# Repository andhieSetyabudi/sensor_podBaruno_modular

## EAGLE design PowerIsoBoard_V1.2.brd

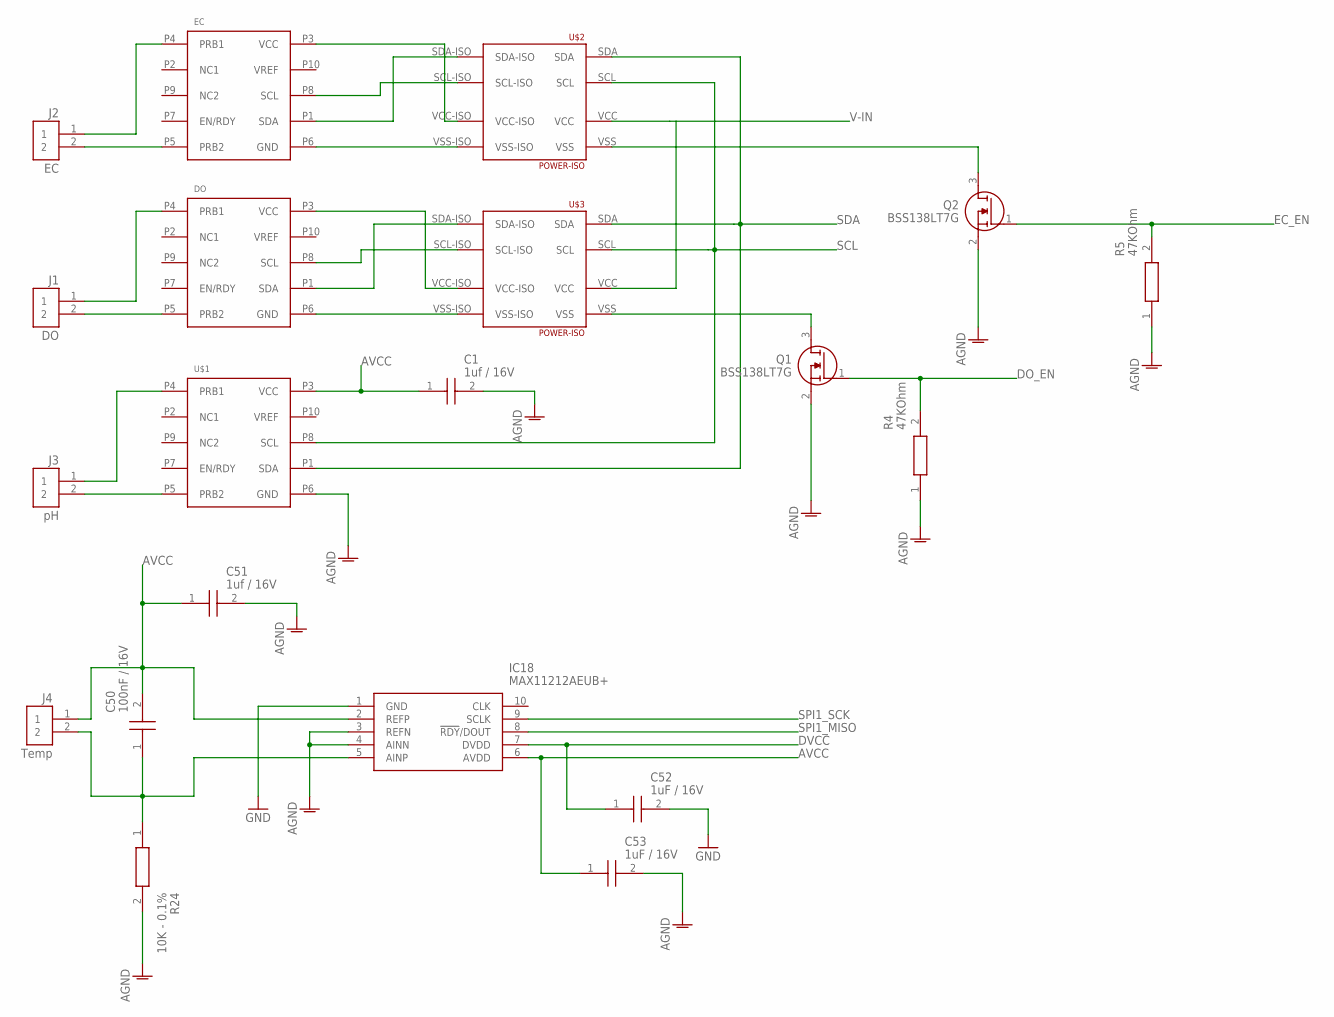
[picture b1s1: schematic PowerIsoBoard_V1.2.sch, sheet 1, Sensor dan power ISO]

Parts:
C1, C51: 1uf / 16V; CAPC1608X90N
C50: 100nF / 16V; CAPC1608X90N
C52, C53: 1uF / 16V; CAPC1608X90N
DO: ATLAS-OEM-SMT; EZO_SMT
EC: ATLAS-OEM-SMT; EZO_SMT
IC18: MAX11212AEUB+; SOP50P490X110-10N
J1: DO; JST_B2B-PH-K-S(LF)(SN)
J2: EC; JST_B2B-PH-K-S(LF)(SN)
J3: pH; JST_B2B-PH-K-S(LF)(SN)
J4: Temp; JST_B2B-PH-K-S(LF)(SN)
Q1, Q2: BSS138LT7G; SOT96P237X111-3N
R4, R5: 47KOhm; RESC1608X55N
R24: 10K - 0.1%; RESC1608X55N
U$1: ATLAS-OEM-SMT; EZO_SMT
U$2, U$3: POWER-ISO; PWR_ISO_TH

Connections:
AGND: C1.2, Q1.2 (S), Q2.2 (S), R4.1, R5.1, U$1.P6 (GND); also elsewhere on the board
AVCC: C1.1, C50.2, C51.1, C53.1, IC18.2 (REFP), IC18.6 (AVDD), J4.1, U$1.P3 (VCC); also elsewhere on the board
DO_EN: Q1.1 (G), R4.2; also elsewhere on the board
DVCC: C52.1, IC18.7 (DVDD); also elsewhere on the board
EC_EN: Q2.1 (G), R5.2; also elsewhere on the board
GND: C51.2, C52.2, C53.2, IC18.1 (GND), IC18.3 (REFN), IC18.4 (AINN), R24.2; also elsewhere on the board
unnamed: C50.1, IC18.5 (AINP), J4.2, R24.1
unnamed: Q1.3 (D), U$3.VSS
unnamed: J3.2, U$1.P5 (PRB2)
unnamed: J3.1, U$1.P4 (PRB1)
unnamed: DO.P5 (PRB2), J1.2
unnamed: DO.P4 (PRB1), J1.1
unnamed: EC.P5 (PRB2), J2.2
unnamed: EC.P4 (PRB1), J2.1
unnamed: EC.P6 (GND), U$2.VSS-ISO
unnamed: EC.P3 (VCC), U$2.VCC-ISO
unnamed: EC.P8 (SCL), U$2.SCL-ISO
unnamed: EC.P1 (SDA), U$2.SDA-ISO
unnamed: DO.P6 (GND), U$3.VSS-ISO
unnamed: DO.P3 (VCC), U$3.VCC-ISO
unnamed: DO.P1 (SDA), U$3.SDA-ISO
unnamed: DO.P8 (SCL), U$3.SCL-ISO
unnamed: Q2.3 (D), U$2.VSS
SCL: U$1.P8 (SCL), U$2.SCL, U$3.SCL; also elsewhere on the board
SDA: U$1.P1 (SDA), U$2.SDA, U$3.SDA; also elsewhere on the board
SPI1_MISO: IC18.8 (!RDY!/DOUT); also elsewhere on the board
SPI1_SCK: IC18.9 (SCLK); also elsewhere on the board
V-IN: U$2.VCC, U$3.VCC; also elsewhere on the board

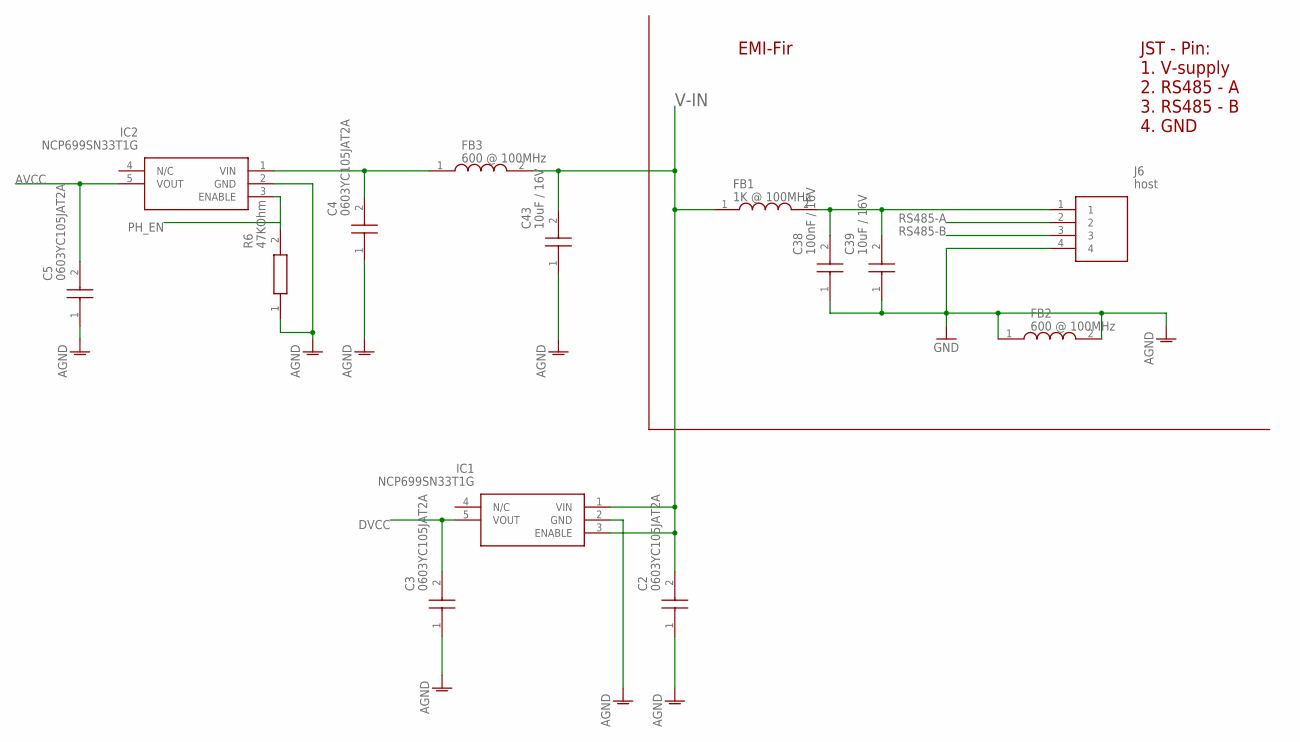
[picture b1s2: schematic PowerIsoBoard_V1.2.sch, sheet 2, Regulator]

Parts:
C2, C3, C4, C5: 0603YC105JAT2A; CAPC1608X90N
C38: 100nF / 16V; CAPC1608X90N
C39, C43: 10uF / 16V; CAPC1608X100N
FB1: 1K @ 100MHz; BLM18KG102SH1J
FB2, FB3: 600 @ 100MHz; BEADC1608X75N
IC1, IC2: NCP699SN33T1G; SOT95P275X110-5N
J6: host; SHDR4W50P0X200_1X4_990X450X600
R6: 47KOhm; RESC1608X55N

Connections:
AGND: C2.1, C3.1, C4.1, C5.1, C43.1, IC1.2 (GND), IC2.2 (GND), R6.1; also elsewhere on the board
AVCC: C5.2, IC2.5 (VOUT); also elsewhere on the board
DVCC: C3.2, IC1.5 (VOUT); also elsewhere on the board
GND: C38.1, C39.1, FB2.1, FB2.2, J6.4; also elsewhere on the board
unnamed: C38.2, C39.2, FB1.2, J6.1
unnamed: C4.2, FB3.1, IC2.1 (VIN)
PH_EN: IC2.3 (ENABLE), R6.2; also elsewhere on the board
RS485-A: J6.2; also elsewhere on the board
RS485-B: J6.3; also elsewhere on the board
V-IN: C2.2, C43.2, FB1.1, FB3.2, IC1.1 (VIN), IC1.3 (ENABLE); also elsewhere on the board

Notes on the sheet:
EMI-Fir
JST - Pin: 1. V-supply 2. RS485 - A 3. RS485 - B 4. GND

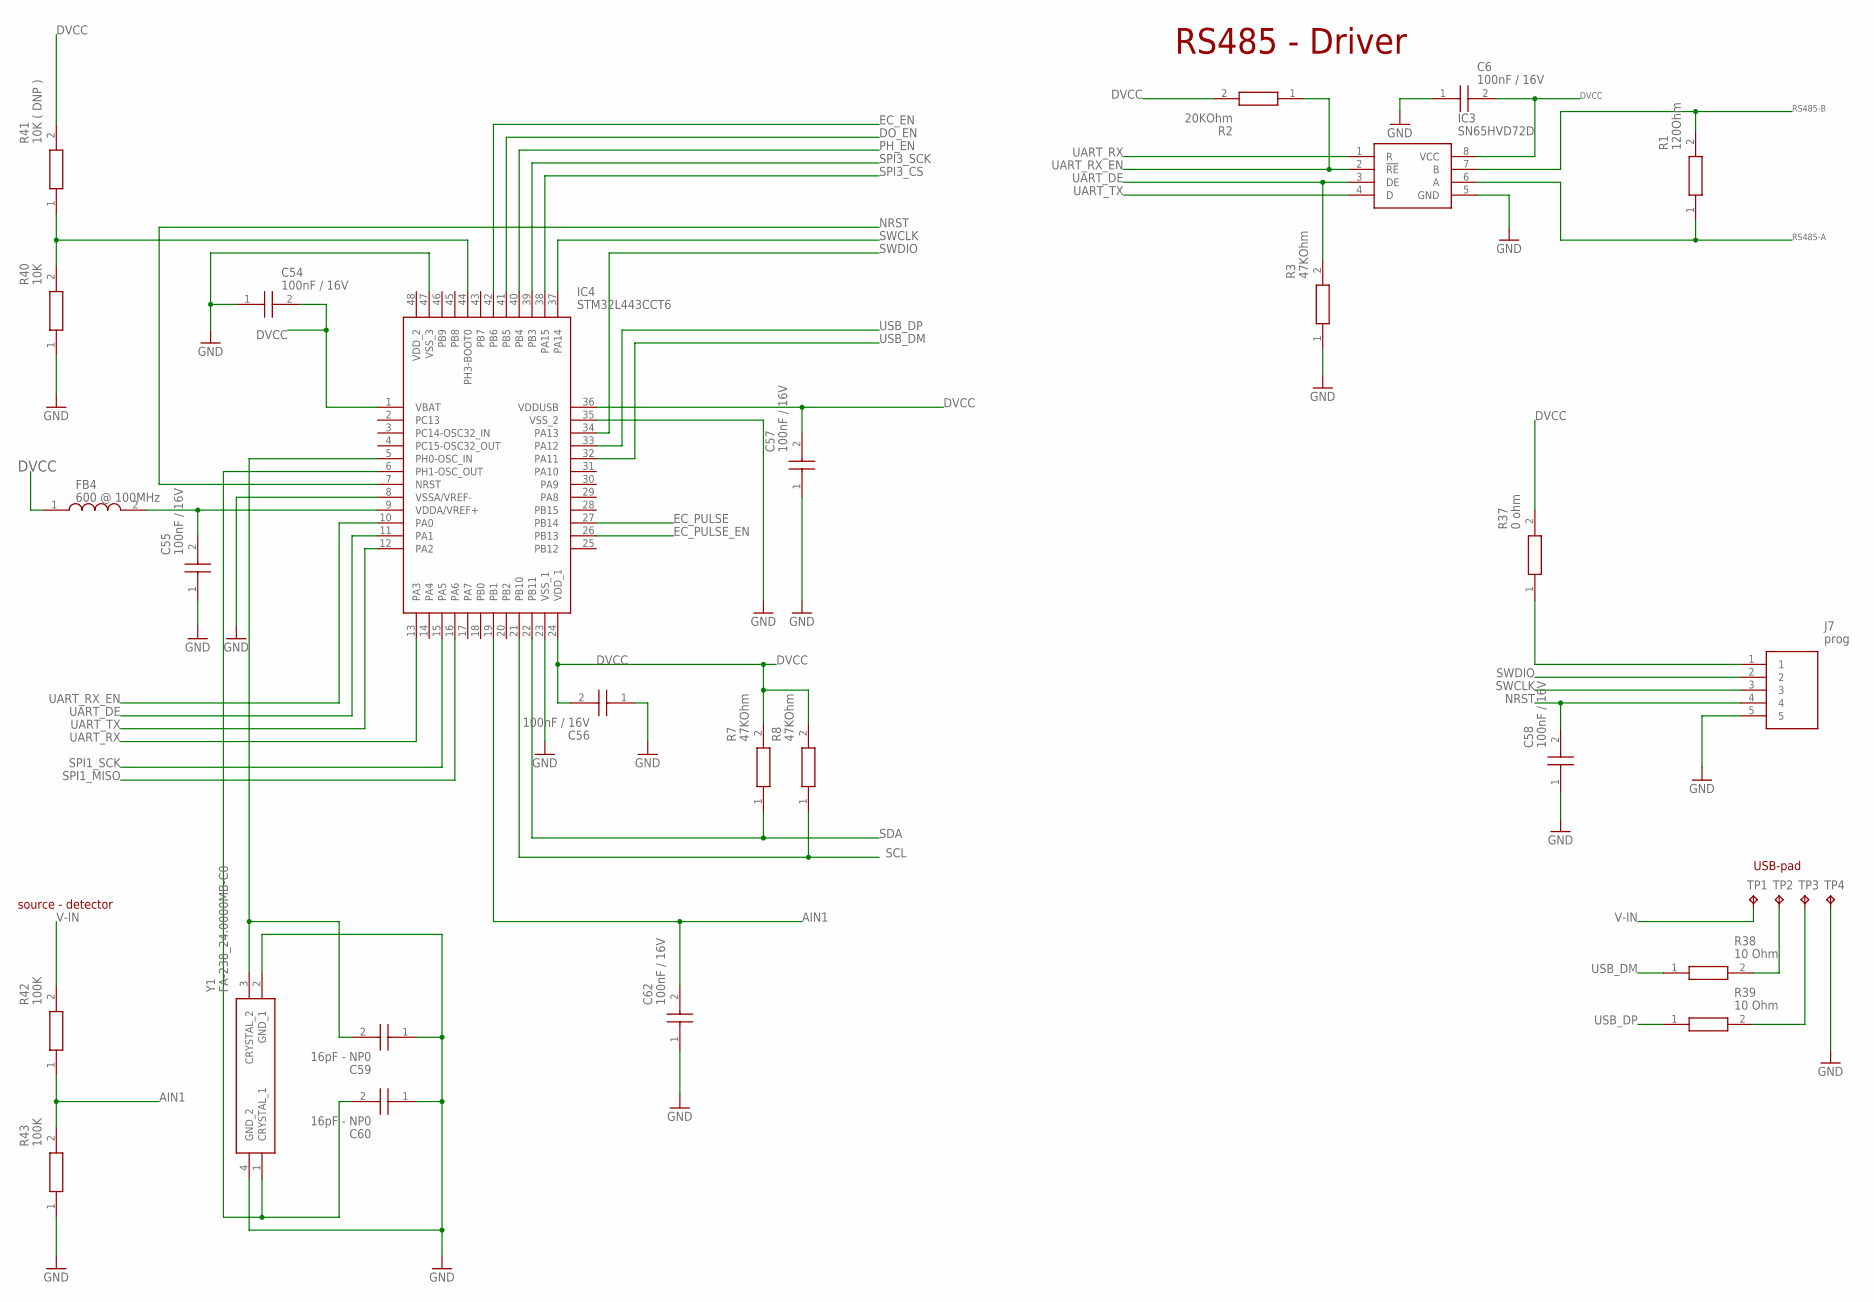
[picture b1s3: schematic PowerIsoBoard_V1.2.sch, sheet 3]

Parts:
C6, C54, C55, C56, C57, C58, C62: 100nF / 16V; CAPC1608X90N
C59, C60: 16pF - NP0; CAPC1608X97N
FB4: 600 @ 100MHz; BEADC1608X75N
IC3: SN65HVD72D; SOIC127P600X175-8N
IC4: STM32L443CCT6; QFP50P900X900X160-48N
J7: prog; SHDR5W50P0X200_1X5_1190X450X60
R1: 120Ohm; RESC1608X55N
R2: 20KOhm; RESC1608X55N
R3, R7, R8: 47KOhm; RESC1608X55N
R37: 0 ohm; RESC1608X55N
R38, R39: 10 Ohm; RESC1608X55N
R40: 10K; RESC1608X55N
R41: 10K ( DNP ); RESC1608X55N
R42, R43: 100K; RESC1608X55N
TP1, TP2, TP3, TP4: TPB1,27; B1,27
Y1: FA-238_24.0000MB-C0; FA238240000MBC0

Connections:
AIN1: C62.2, IC4.19 (PB1), R42.1, R43.2
DO_EN: IC4.41 (PB5); also elsewhere on the board
DVCC: C6.2, C54.2, C56.2, C57.2, FB4.1, IC3.8 (VCC), IC4.1 (VBAT), IC4.24 (VDD_1), IC4.36 (VDDUSB), R2.2, R7.2, R8.2, R37.2, R41.2; also elsewhere on the board
EC_EN: IC4.42 (PB6); also elsewhere on the board
EC_PULSE: IC4.27 (PB14)
EC_PULSE_EN: IC4.26 (PB13)
GND: C6.1, C54.1, C55.1, C56.1, C57.1, C58.1, C59.1, C60.1, C62.1, IC3.5 (GND), IC4.8 (VSSA/VREF-), IC4.23 (VSS_1), IC4.35 (VSS_2), IC4.47 (VSS_3), J7.5, R3.1, R40.1, R43.1, TP4.TP, Y1.2 (GND_1), Y1.4 (GND_2); also elsewhere on the board
unnamed: J7.1, R37.1
unnamed: R38.2, TP2.TP
unnamed: R39.2, TP3.TP
unnamed: IC4.44 (PH3-BOOT0), R40.2, R41.1
unnamed: C60.2, IC4.6 (PH1-OSC_OUT), Y1.1 (CRYSTAL_1)
unnamed: C59.2, IC4.5 (PH0-OSC_IN), Y1.3 (CRYSTAL_2)
unnamed: C55.2, FB4.2, IC4.9 (VDDA/VREF+)
NRST: C58.2, IC4.7 (NRST), J7.4
PH_EN: IC4.40 (PB4); also elsewhere on the board
RS485-A: IC3.6 (A), R1.1; also elsewhere on the board
RS485-B: IC3.7 (B), R1.2; also elsewhere on the board
SCL: IC4.21 (PB10), R8.1; also elsewhere on the board
SDA: IC4.22 (PB11), R7.1; also elsewhere on the board
SPI1_MISO: IC4.16 (PA6); also elsewhere on the board
SPI1_SCK: IC4.15 (PA5); also elsewhere on the board
SPI3_CS: IC4.38 (PA15)
SPI3_SCK: IC4.39 (PB3)
SWCLK: IC4.37 (PA14), J7.3
SWDIO: IC4.34 (PA13), J7.2
UART_DE: IC3.3 (DE), IC4.11 (PA1), R3.2
UART_RX: IC3.1 (R), IC4.13 (PA3)
UART_RX_EN: IC3.2 (!RE), IC4.10 (PA0), R2.1
UART_TX: IC3.4 (D), IC4.12 (PA2)
USB_DM: IC4.32 (PA11), R38.1
USB_DP: IC4.33 (PA12), R39.1
V-IN: R42.2, TP1.TP; also elsewhere on the board

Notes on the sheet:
RS485 - Driver
USB-pad
source - detector

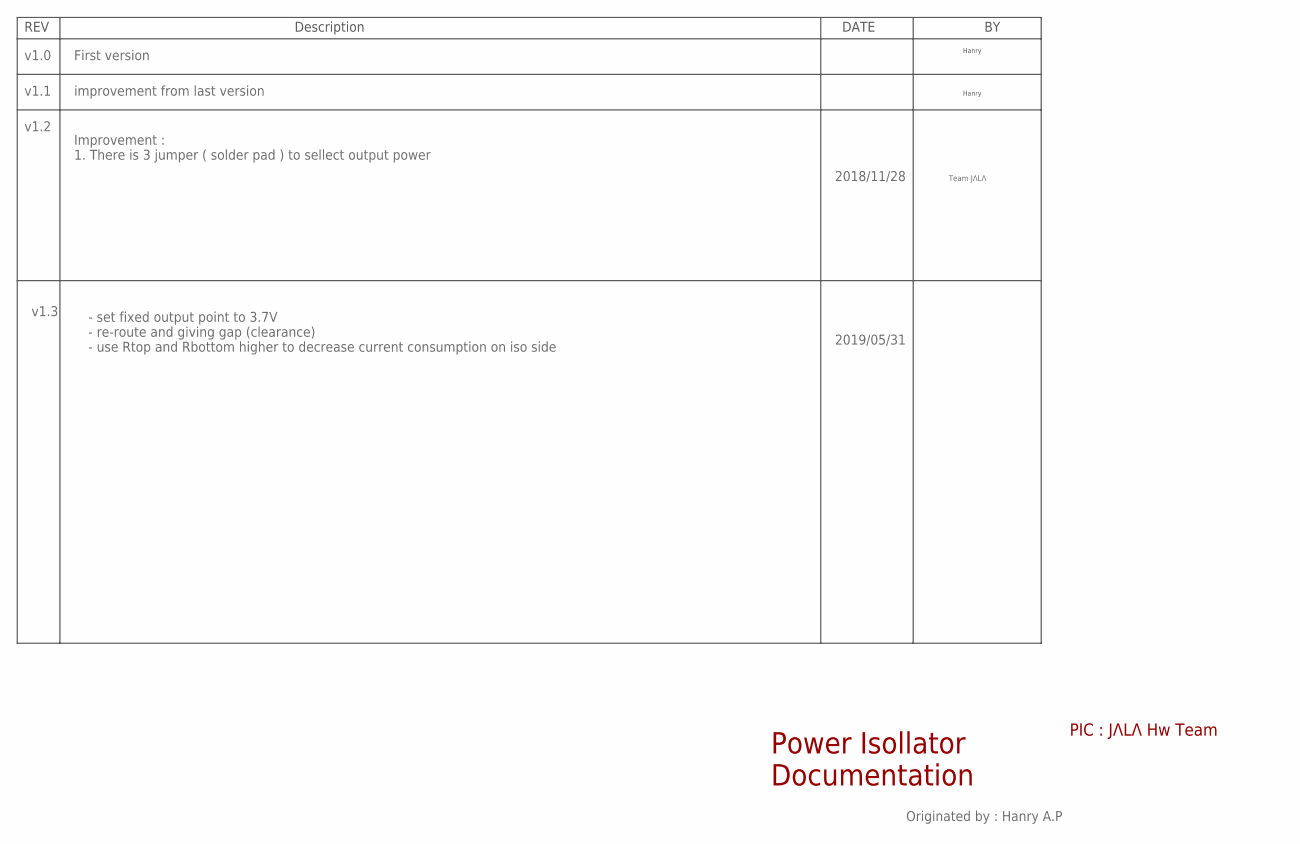
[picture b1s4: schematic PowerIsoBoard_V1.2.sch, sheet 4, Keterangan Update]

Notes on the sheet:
PIC : JΛLΛ Hw Team
Power Isollator Documentation
Hanry
Team JΛLΛ
v1.0
v1.1
v1.2
2018/11/28
First version
improvement from last version
Improvement : 1. There is 3 jumper ( solder pad ) to sellect output power
Originated by : Hanry A.P
v1.3
- set fixed output point to 3.7V - re-route and giving gap (clearance) - use Rtop and Rbottom higher to decrease current consumption on iso side
2019/05/31

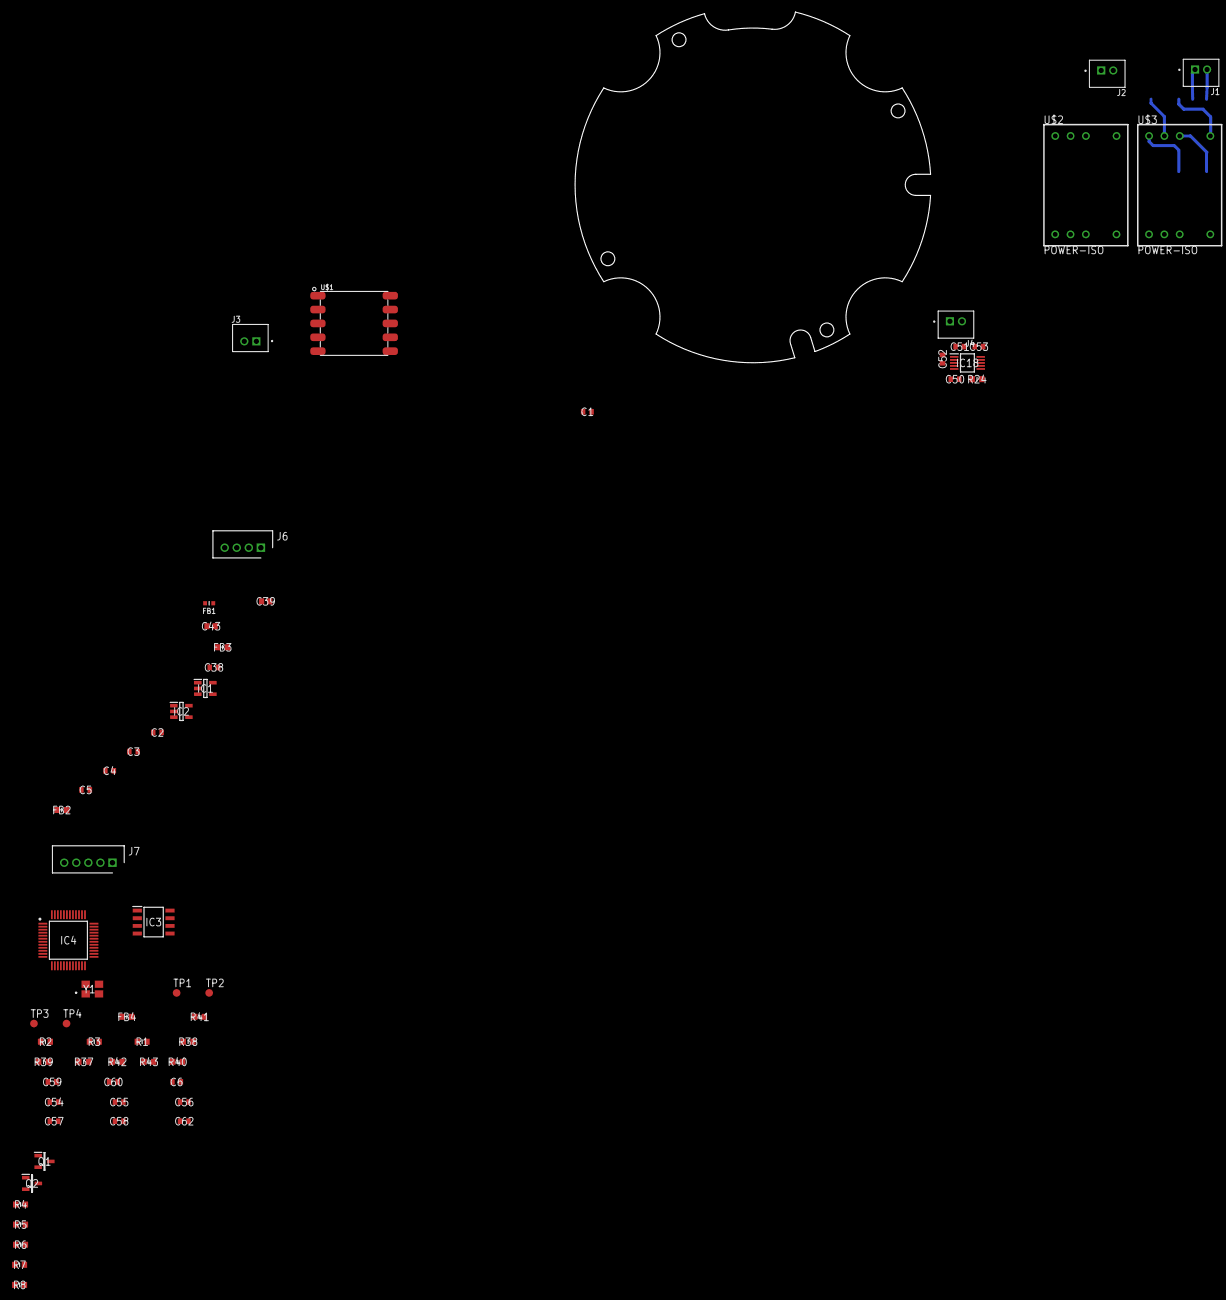
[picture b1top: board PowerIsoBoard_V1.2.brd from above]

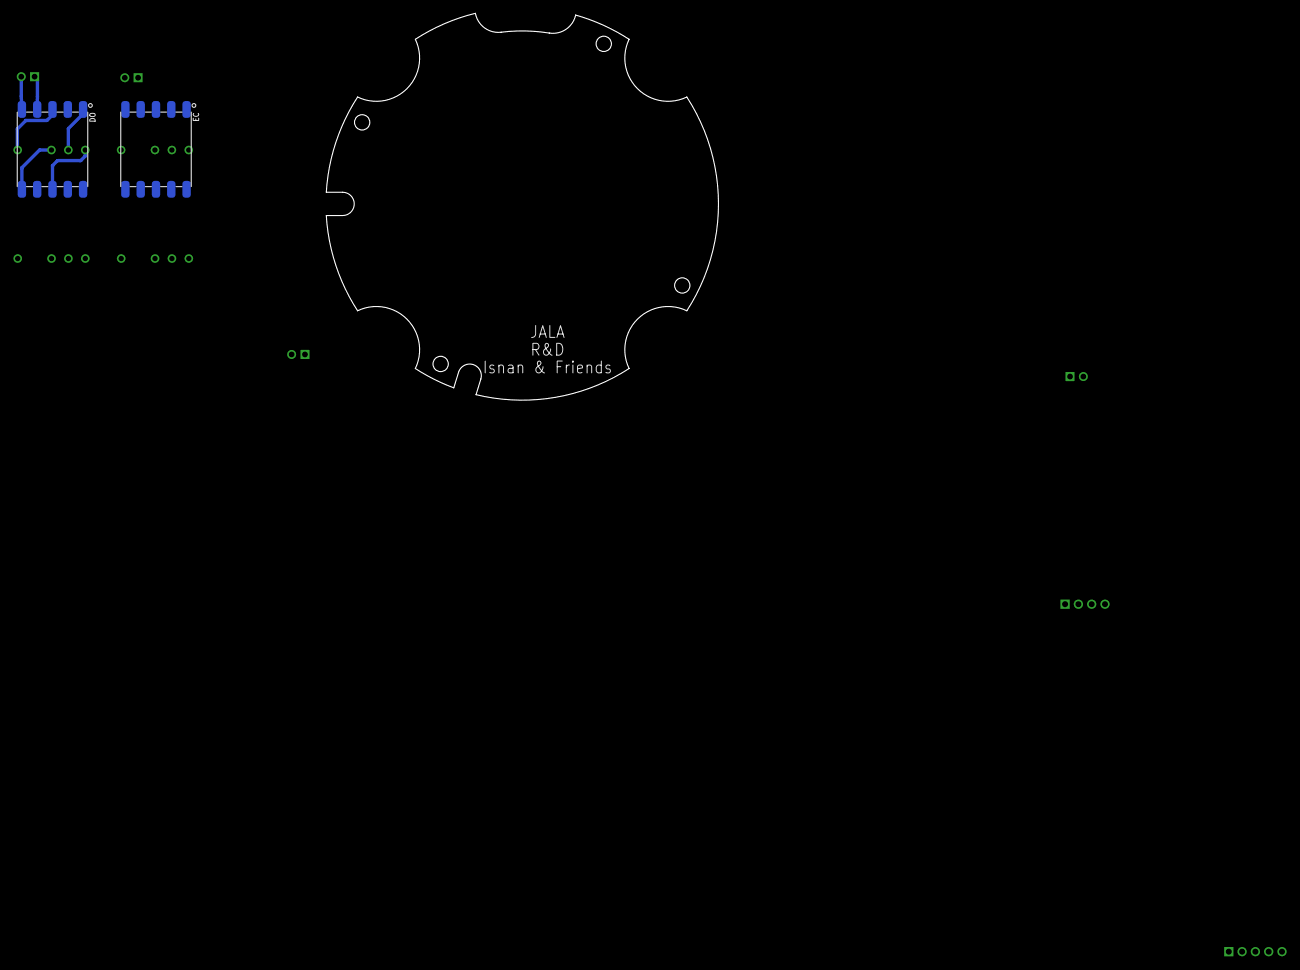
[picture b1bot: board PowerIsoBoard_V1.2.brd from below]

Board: 2 copper layers, 58.9 x 58.1 mm, 64 parts (2 on the bottom side), 50 nets.
